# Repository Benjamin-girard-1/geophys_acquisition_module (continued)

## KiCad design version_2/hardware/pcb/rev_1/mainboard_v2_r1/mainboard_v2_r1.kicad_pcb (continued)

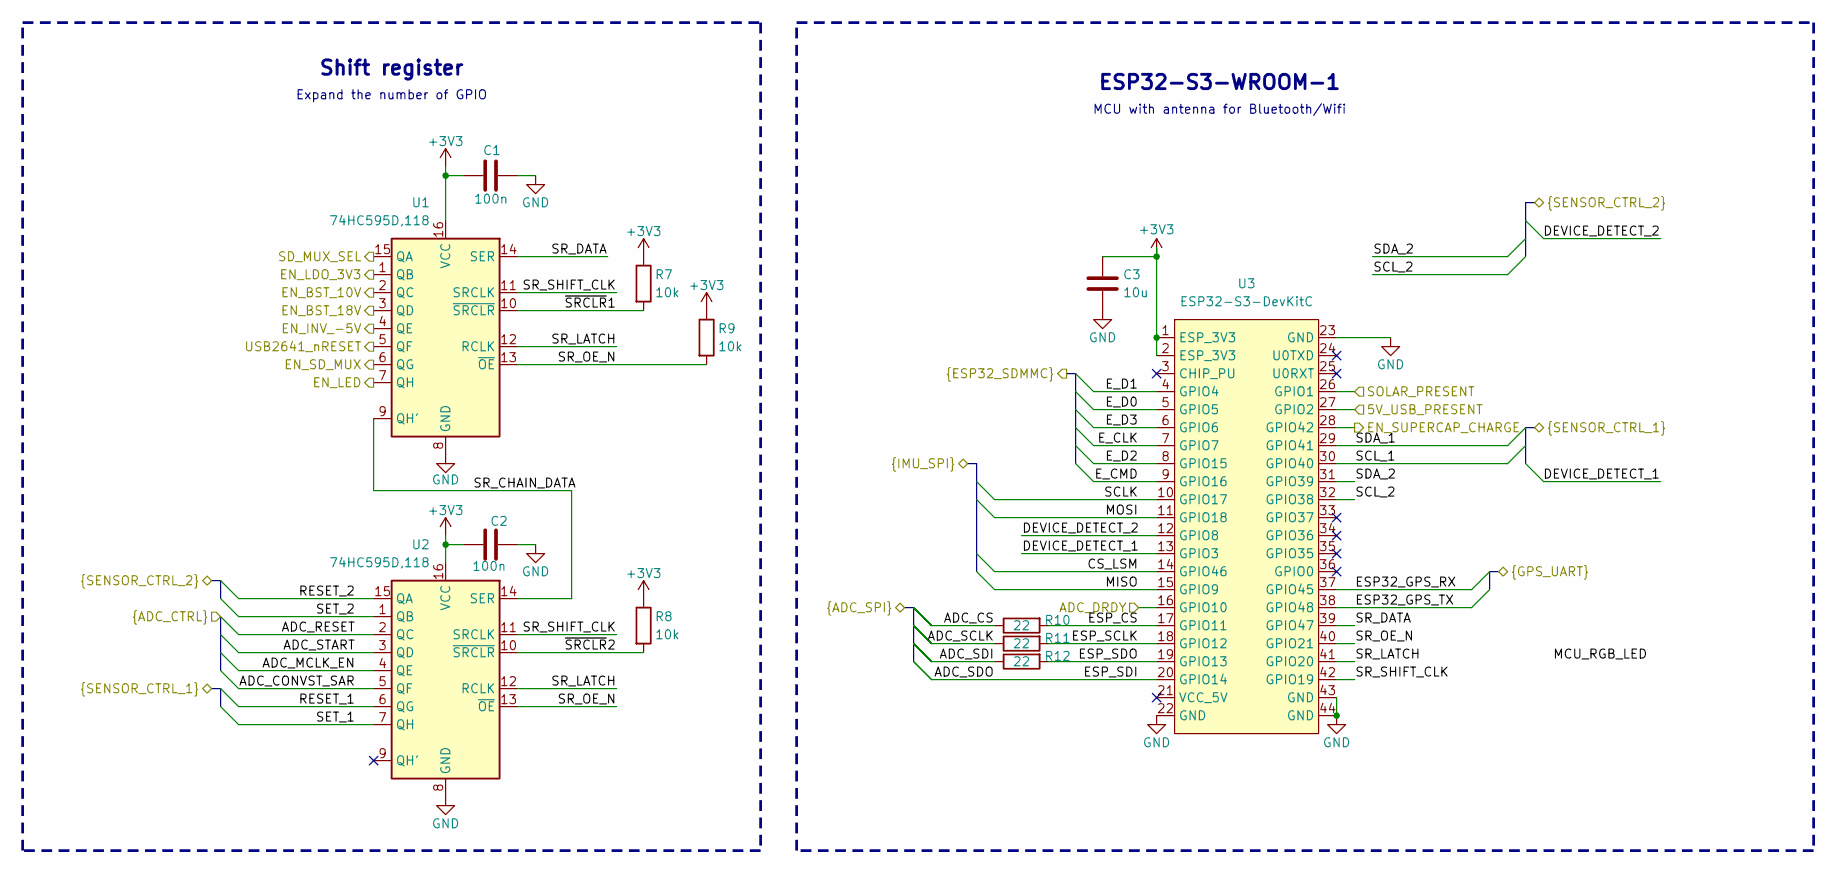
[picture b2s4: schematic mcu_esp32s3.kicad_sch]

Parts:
C1, C2: 100n; C_0603_1608Metric; LCSC C14663
C3: 10u; C_0805_2012Metric; LCSC C15850
R7, R8, R9: 10k; R_0603_1608Metric; LCSC C25804
R10, R11, R12: 22; R_0603_1608Metric; LCSC C23345
U1, U2: 74HC595D,118; SOIC-16_3.9x9.9mm_P1.27mm; LCSC C5947
U3: ESP32-S3-DevKitC; MODULE_ESP32-S3-DEVKITC

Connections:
+3V3: C1.1, C2.1, C3.1, R7.1, R8.1, R9.1, U1.16 (VCC), U2.16 (VCC), U3.1 (ESP_3V3), U3.2 (ESP_3V3); also elsewhere on the board
/ADC_AD777x/ADC_CONVST_SAR: U2.5 (QF); also elsewhere on the board
/ADC_AD777x/ADC_CS: R10.1; also elsewhere on the board
/ADC_AD777x/ADC_DRDY: U3.16 (GPIO10); also elsewhere on the board
/ADC_AD777x/ADC_MCLK_EN: U2.4 (QE); also elsewhere on the board
/ADC_AD777x/ADC_RESET: U2.2 (QC); also elsewhere on the board
/ADC_AD777x/ADC_SCLK: R11.1; also elsewhere on the board
/ADC_AD777x/ADC_SDI: R12.1; also elsewhere on the board
/ADC_AD777x/ADC_SDO: U3.20 (GPIO14); also elsewhere on the board
/ADC_AD777x/ADC_START: U2.3 (QD); also elsewhere on the board
/DATA_SAVING/EN_SD_MUX: U1.6 (QG); also elsewhere on the board
/DATA_SAVING/E_CLK: U3.7 (GPIO7); also elsewhere on the board
/DATA_SAVING/E_CMD: U3.9 (GPIO16); also elsewhere on the board
/DATA_SAVING/E_D0: U3.5 (GPIO5); also elsewhere on the board
/DATA_SAVING/E_D1: U3.4 (GPIO4); also elsewhere on the board
/DATA_SAVING/E_D2: U3.8 (GPIO15); also elsewhere on the board
/DATA_SAVING/E_D3: U3.6 (GPIO6); also elsewhere on the board
/DATA_SAVING/SD_MUX_SEL: U1.15 (QA); also elsewhere on the board
/DATA_SAVING/USB2641_nRESET: U1.5 (QF); also elsewhere on the board
/DEVICE_DETECT_1: U3.13 (GPIO3); also elsewhere on the board
/DEVICE_DETECT_2: U3.12 (GPIO8); also elsewhere on the board
/GNSS/ESP32_GPS_RX: U3.37 (GPIO45); also elsewhere on the board
/GNSS/ESP32_GPS_TX: U3.38 (GPIO48); also elsewhere on the board
/IMU/CS_LSM: U3.14 (GPIO46); also elsewhere on the board
/IMU/MISO: U3.15 (GPIO9); also elsewhere on the board
/IMU/MOSI: U3.11 (GPIO18); also elsewhere on the board
/IMU/SCLK: U3.10 (GPIO17); also elsewhere on the board
/IO_CONNECTOR/EN_LED: U1.7 (QH); also elsewhere on the board
/MCU_ESP32S3/5V_USB_PRESENT: U3.27 (GPIO2); also elsewhere on the board
/MCU_ESP32S3/EN_BST_10V: U1.2 (QC); also elsewhere on the board
/MCU_ESP32S3/EN_BST_18V: U1.3 (QD); also elsewhere on the board
/MCU_ESP32S3/EN_INV_-5V: U1.4 (QE); also elsewhere on the board
/MCU_ESP32S3/EN_LDO_3V3: U1.1 (QB); also elsewhere on the board
/MCU_ESP32S3/EN_SUPERCAP_CHARGE: U3.28 (GPIO42); also elsewhere on the board
/MCU_ESP32S3/ESP_CS: R10.2, U3.17 (GPIO11)
/MCU_ESP32S3/ESP_SCLK: R11.2, U3.18 (GPIO12)
/MCU_ESP32S3/ESP_SDO: R12.2, U3.19 (GPIO13)
/MCU_ESP32S3/SOLAR_PRESENT: U3.26 (GPIO1); also elsewhere on the board
/MCU_ESP32S3/SR_CHAIN_DATA: U1.9 (QH'), U2.14 (SER)
/MCU_ESP32S3/SR_DATA: U1.14 (SER), U3.39 (GPIO47)
/MCU_ESP32S3/SR_LATCH: U1.12 (RCLK), U2.12 (RCLK), U3.41 (GPIO20)
/MCU_ESP32S3/SR_OE_N: R9.2, U1.13 (~OE), U2.13 (~OE), U3.40 (GPIO21)
/MCU_ESP32S3/SR_SHIFT_CLK: U1.11 (SRCLK), U2.11 (SRCLK), U3.42 (GPIO19)
/MCU_ESP32S3/~SRCLR1: R7.2, U1.10 (~SRCLR)
/MCU_ESP32S3/~SRCLR2: R8.2, U2.10 (~SRCLR)
/RESET_1: U2.6 (QG); also elsewhere on the board
/RESET_2: U2.15 (QA); also elsewhere on the board
/SCL_1: U3.30 (GPIO40); also elsewhere on the board
/SCL_2: U3.32 (GPIO38); also elsewhere on the board
/SDA_1: U3.29 (GPIO41); also elsewhere on the board
/SDA_2: U3.31 (GPIO39); also elsewhere on the board
/SET_1: U2.7 (QH); also elsewhere on the board
/SET_2: U2.1 (QB); also elsewhere on the board
GND: C1.2, C2.2, C3.2, U1.8 (GND), U2.8 (GND), U3.22 (GND), U3.23 (GND), U3.43 (GND), U3.44 (GND); also elsewhere on the board

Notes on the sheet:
Shift register
Expand the number of GPIO
ESP32-S3-WROOM-1
MCU with antenna for Bluetooth/Wifi

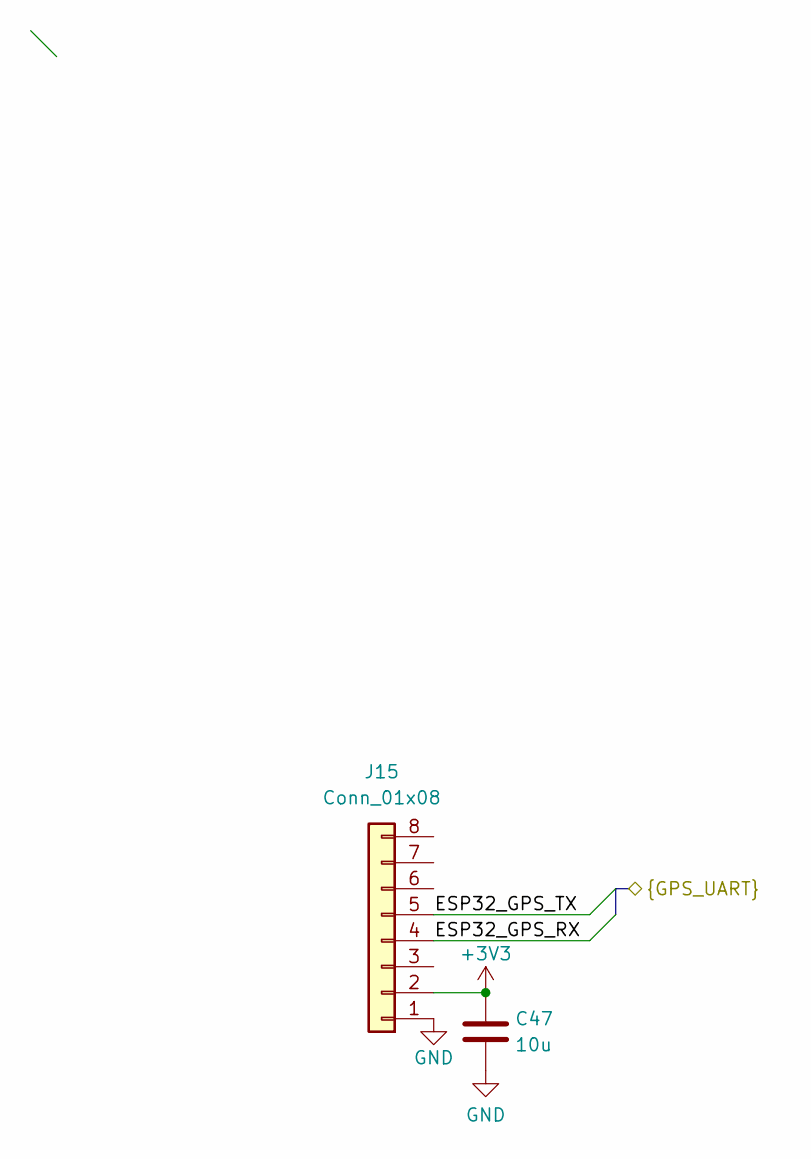
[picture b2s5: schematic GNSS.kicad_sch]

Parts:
C47: 10u; C_0805_2012Metric; LCSC C15850
J15: Conn_01x08; MAX_M10S_WITH_HEADER

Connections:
+3V3: C47.1, J15.2; also elsewhere on the board
/GNSS/ESP32_GPS_RX: J15.4; also elsewhere on the board
/GNSS/ESP32_GPS_TX: J15.5; also elsewhere on the board
GND: C47.2, J15.1; also elsewhere on the board

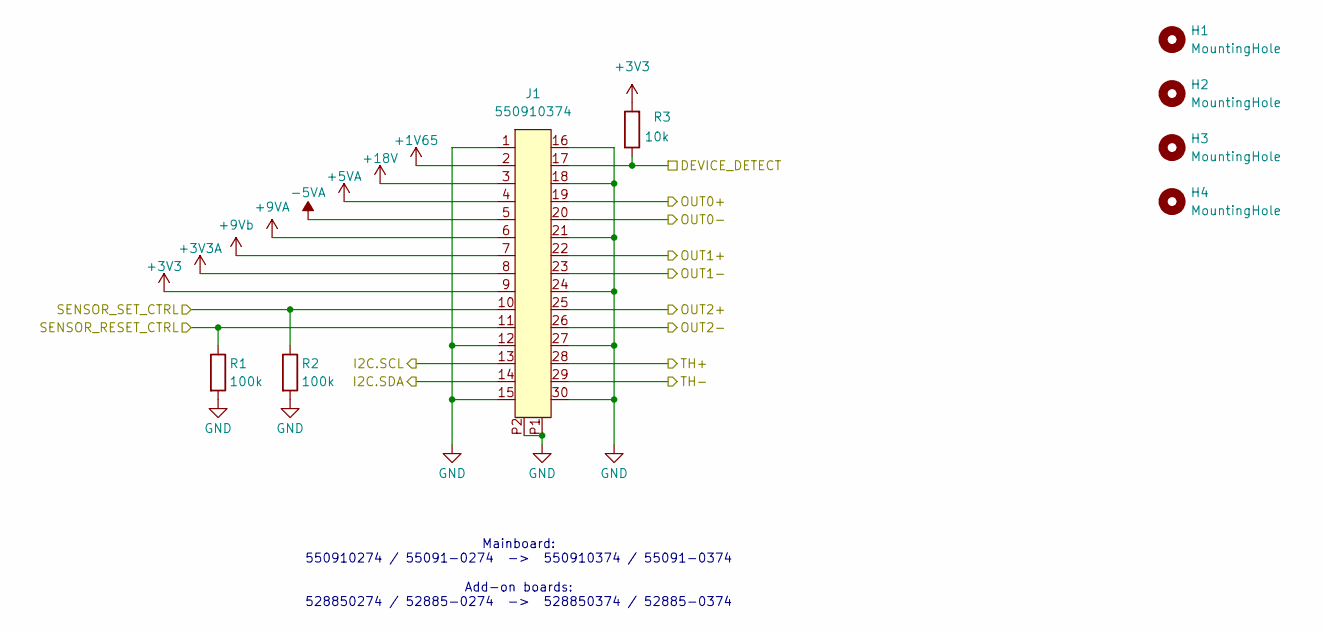
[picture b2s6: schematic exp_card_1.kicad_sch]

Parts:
H1, H2, H3, H4: MountingHole; MountingHole_4.3mm_M4
J1: 550910374; CON_550910374_MOL
R1, R2: 100k; R_0603_1608Metric; LCSC C25803
R3: 10k; R_0603_1608Metric; LCSC C25804

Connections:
+1V65: J1.2; also elsewhere on the board
+3V3: J1.9, R3.2; also elsewhere on the board
+3V3A: J1.8; also elsewhere on the board
+5VA: J1.4; also elsewhere on the board
+9VA: J1.6; also elsewhere on the board
+9Vb: J1.7; also elsewhere on the board
+18V: J1.3; also elsewhere on the board
-5VA: J1.5; also elsewhere on the board
/ADC_AD777x/AIN0+: J1.25; also elsewhere on the board
/ADC_AD777x/AIN0-: J1.26; also elsewhere on the board
/ADC_AD777x/AIN1+: J1.22; also elsewhere on the board
/ADC_AD777x/AIN1-: J1.23; also elsewhere on the board
/ADC_AD777x/AIN2+: J1.19; also elsewhere on the board
/ADC_AD777x/AIN2-: J1.20; also elsewhere on the board
/ADC_AD777x/TH1+: J1.28; also elsewhere on the board
/ADC_AD777x/TH1-: J1.29; also elsewhere on the board
/DEVICE_DETECT_1: J1.17, R3.1; also elsewhere on the board
/RESET_1: J1.11, R1.1; also elsewhere on the board
/SCL_1: J1.13; also elsewhere on the board
/SDA_1: J1.14; also elsewhere on the board
/SET_1: J1.10, R2.1; also elsewhere on the board
GND: J1.1, J1.12, J1.15, J1.16, J1.18, J1.21, J1.24, J1.27, J1.30, J1.P1, J1.P2, R1.2, R2.2; also elsewhere on the board

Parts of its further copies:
H5, H6, H7, H8: MountingHole; MountingHole_4.3mm_M4
J2: 550910374; CON_550910374_MOL
R4, R5: 100k; R_0603_1608Metric; LCSC C25803
R6: 10k; R_0603_1608Metric; LCSC C25804

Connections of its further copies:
+1V65: J2.2; also elsewhere on the board
+3V3: J2.9, R6.2; also elsewhere on the board
+3V3A: J2.8; also elsewhere on the board
+5VA: J2.4; also elsewhere on the board
+9VA: J2.6; also elsewhere on the board
+9Vb: J2.7; also elsewhere on the board
+18V: J2.3; also elsewhere on the board
-5VA: J2.5; also elsewhere on the board
/ADC_AD777x/AIN4+: J2.25; also elsewhere on the board
/ADC_AD777x/AIN4-: J2.26; also elsewhere on the board
/ADC_AD777x/AIN5+: J2.22; also elsewhere on the board
/ADC_AD777x/AIN5-: J2.23; also elsewhere on the board
/ADC_AD777x/AIN6+: J2.19; also elsewhere on the board
/ADC_AD777x/AIN6-: J2.20; also elsewhere on the board
/ADC_AD777x/TH2+: J2.28; also elsewhere on the board
/ADC_AD777x/TH2-: J2.29; also elsewhere on the board
/DEVICE_DETECT_2: J2.17, R6.1; also elsewhere on the board
/RESET_2: J2.11, R4.1; also elsewhere on the board
/SCL_2: J2.13; also elsewhere on the board
/SDA_2: J2.14; also elsewhere on the board
/SET_2: J2.10, R5.1; also elsewhere on the board
GND: J2.1, J2.12, J2.15, J2.16, J2.18, J2.21, J2.24, J2.27, J2.30, J2.P1, J2.P2, R4.2, R5.2; also elsewhere on the board

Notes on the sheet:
Mainboard: 550910274 / 55091-0274 -> 550910374 / 55091-0374 Add-on boards: 528850274 / 52885-0274 -> 528850374 / 52885-0374

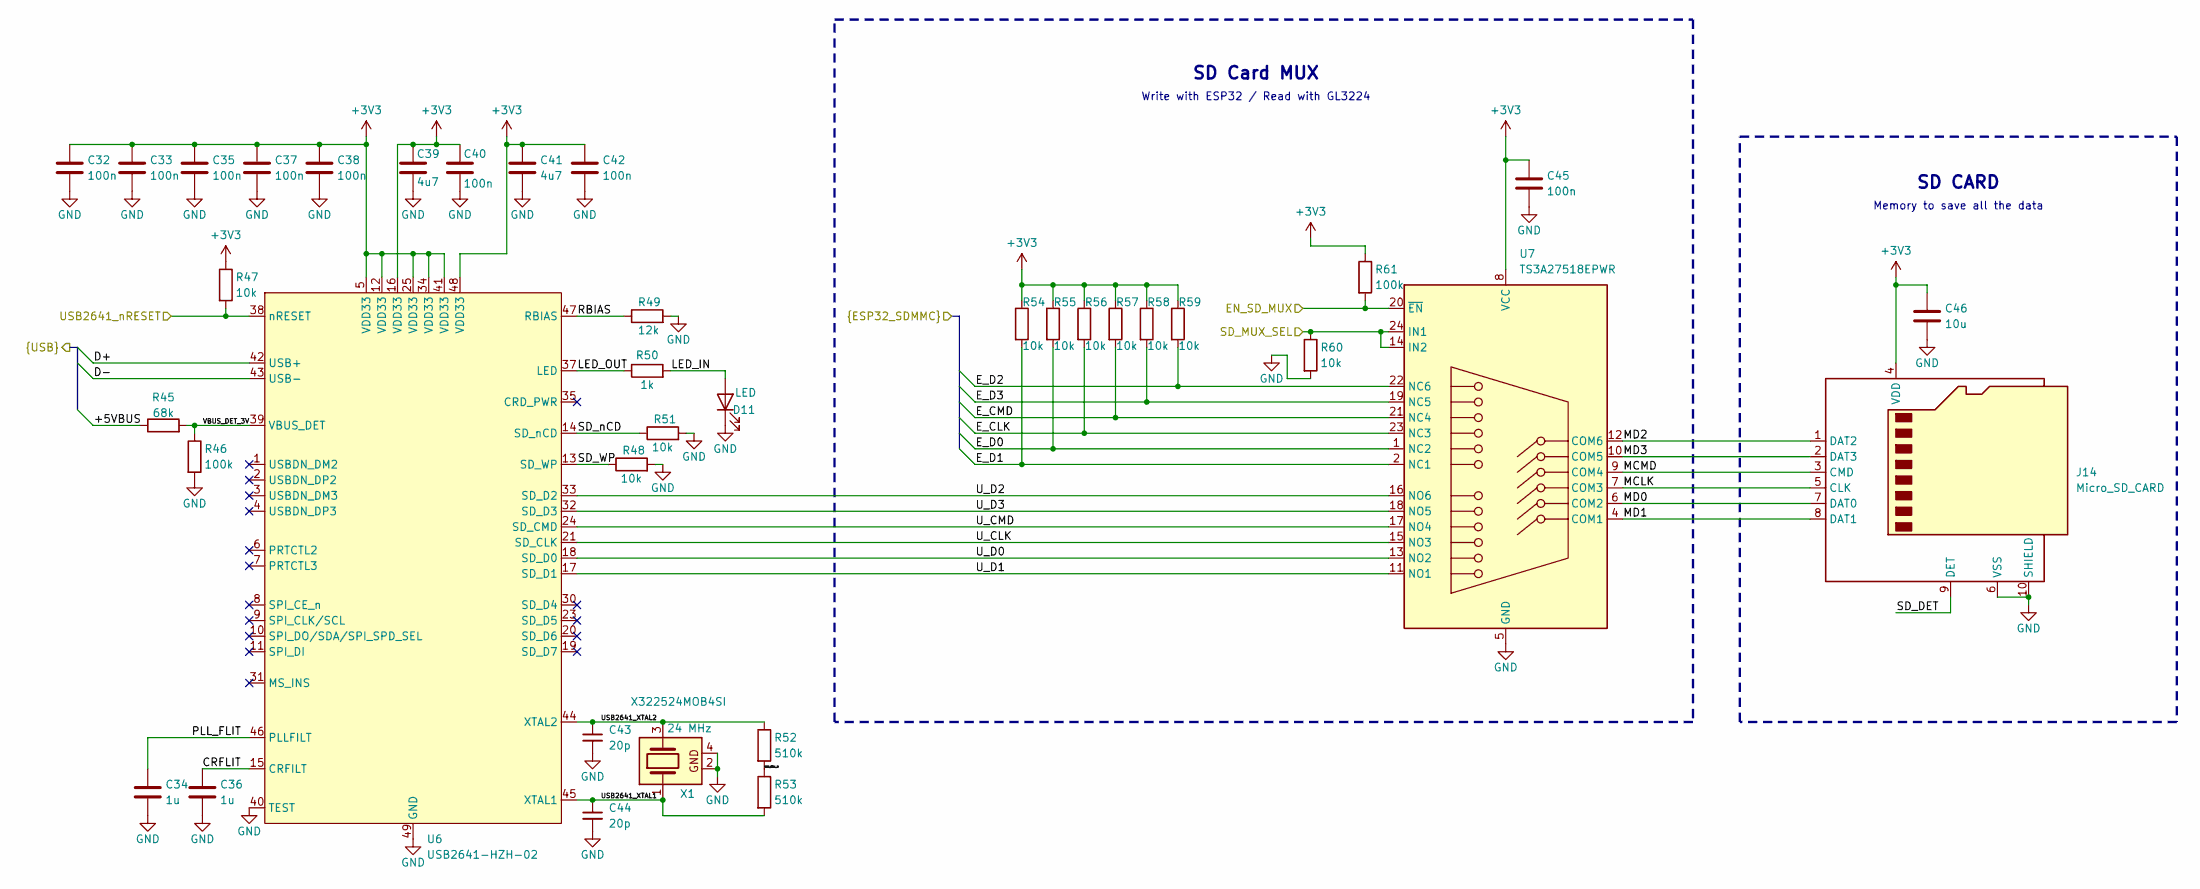
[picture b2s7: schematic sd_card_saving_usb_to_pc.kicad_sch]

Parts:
C32, C33, C35, C37, C38, C40, C42, C45: 100n; C_0603_1608Metric; LCSC C14663
C34, C36: 1u; C_0805_2012Metric; LCSC C28323
C39, C41: 4u7; C_1206_3216Metric; LCSC C29823
C43, C44: 20p; C_0402_1005Metric; LCSC C1554
C46: 10u; C_0805_2012Metric; LCSC C15850
D11: LED; LED_0805_2012Metric; LCSC C2296
J14: Micro_SD_CARD; CONN_503398-1892_MOL; LCSC C428492
R45: 68k; R_0603_1608Metric; LCSC C23231
R46, R61: 100k; R_0603_1608Metric; LCSC C25803
R47, R48, R51, R54, R55, R56, R57, R58, R59, R60: 10k; R_0603_1608Metric; LCSC C25804
R49: 12k; R_0603_1608Metric; LCSC C22790
R50: 1k; R_0603_1608Metric; LCSC C21190
R52, R53: 510k; R_0603_1608Metric; LCSC C23192
U6: USB2641-HZH-02; QFN-48-1EP_7x7mm_P0.5mm_EP5.3x5.3mm; LCSC C633596
U7: TS3A27518EPWR; TSSOP-24_4.4x7.8mm_P0.65mm; LCSC C443721
X1: X322524MOB4SI; Crystal_SMD_3225-4Pin_3.2x2.5mm; LCSC C70590

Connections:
+3V3: C32.1, C33.1, C35.1, C37.1, C38.1, C39.1, C40.1, C41.1, C42.1, C45.1, C46.1, J14.4 (VDD), R47.1, R54.1, R55.1, R56.1, R57.1, R58.1, R59.1, R61.1, U6.5 (VDD33), U6.12 (VDD33), U6.16 (VDD33), U6.25 (VDD33), U6.34 (VDD33), U6.41 (VDD33), U6.48 (VDD33), U7.8 (VCC); also elsewhere on the board
/DATA_SAVING/+5VBUS: R45.1; also elsewhere on the board
/DATA_SAVING/CRFLIT: C36.1, U6.15 (CRFILT)
/DATA_SAVING/D+: U6.42 (USB+); also elsewhere on the board
/DATA_SAVING/D-: U6.43 (USB-); also elsewhere on the board
/DATA_SAVING/EN_SD_MUX: R61.2, U7.20 (~EN); also elsewhere on the board
/DATA_SAVING/E_CLK: R56.2, U7.23 (NC3); also elsewhere on the board
/DATA_SAVING/E_CMD: R57.2, U7.21 (NC4); also elsewhere on the board
/DATA_SAVING/E_D0: R55.2, U7.1 (NC2); also elsewhere on the board
/DATA_SAVING/E_D1: R54.2, U7.2 (NC1); also elsewhere on the board
/DATA_SAVING/E_D2: R59.2, U7.22 (NC6); also elsewhere on the board
/DATA_SAVING/E_D3: R58.2, U7.19 (NC5); also elsewhere on the board
/DATA_SAVING/LED_IN: D11.2 (A), R50.2
/DATA_SAVING/LED_OUT: R50.1, U6.37 (LED)
/DATA_SAVING/MCLK: J14.5 (CLK), U7.7 (COM3)
/DATA_SAVING/MCMD: J14.3 (CMD), U7.9 (COM4)
/DATA_SAVING/MD0: J14.7 (DAT0), U7.6 (COM2)
/DATA_SAVING/MD1: J14.8 (DAT1), U7.4 (COM1)
/DATA_SAVING/MD2: J14.1 (DAT2), U7.12 (COM6)
/DATA_SAVING/MD3: J14.2 (DAT3), U7.10 (COM5)
/DATA_SAVING/PLL_FLIT: C34.1, U6.46 (PLLFILT)
/DATA_SAVING/RBIAS: R49.1, U6.47 (RBIAS)
/DATA_SAVING/SD_DET: J14.9 (DET)
/DATA_SAVING/SD_MUX_SEL: R60.1, U7.14 (IN2), U7.24 (IN1); also elsewhere on the board
/DATA_SAVING/SD_WP: R48.1, U6.13 (SD_WP)
/DATA_SAVING/SD_nCD: R51.1, U6.14 (SD_nCD)
/DATA_SAVING/USB2641_XTAL1: C44.1, R53.2, U6.45 (XTAL1), X1.1
/DATA_SAVING/USB2641_XTAL2: C43.1, R52.1, U6.44 (XTAL2), X1.3
/DATA_SAVING/USB2641_nRESET: R47.2, U6.38 (nRESET); also elsewhere on the board
/DATA_SAVING/USB_XTAL_R: R52.2, R53.1
/DATA_SAVING/U_CLK: U6.21 (SD_CLK), U7.15 (NO3)
/DATA_SAVING/U_CMD: U6.24 (SD_CMD), U7.17 (NO4)
/DATA_SAVING/U_D0: U6.18 (SD_D0), U7.13 (NO2)
/DATA_SAVING/U_D1: U6.17 (SD_D1), U7.11 (NO1)
/DATA_SAVING/U_D2: U6.33 (SD_D2), U7.16 (NO6)
/DATA_SAVING/U_D3: U6.32 (SD_D3), U7.18 (NO5)
/DATA_SAVING/VBUS_DET_3V: R45.2, R46.1, U6.39 (VBUS_DET)
GND: C32.2, C33.2, C34.2, C35.2, C36.2, C37.2, C38.2, C39.2, C40.2, C41.2, C42.2, C43.2, C44.2, C45.2, C46.2, D11.1 (K), J14.6 (VSS), J14.10 (SHIELD), J14.11 (VSS), J14.12 (VSS), J14.13 (VSS), J14.14 (VSS), R46.2, R48.2, R49.2, R51.2, R60.2, U6.40 (TEST), U6.49 (GND), U7.5 (GND), X1.2, X1.4; also elsewhere on the board

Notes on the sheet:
SD CARD
SD Card MUX
Memory to save all the data
Write with ESP32 / Read with GL3224

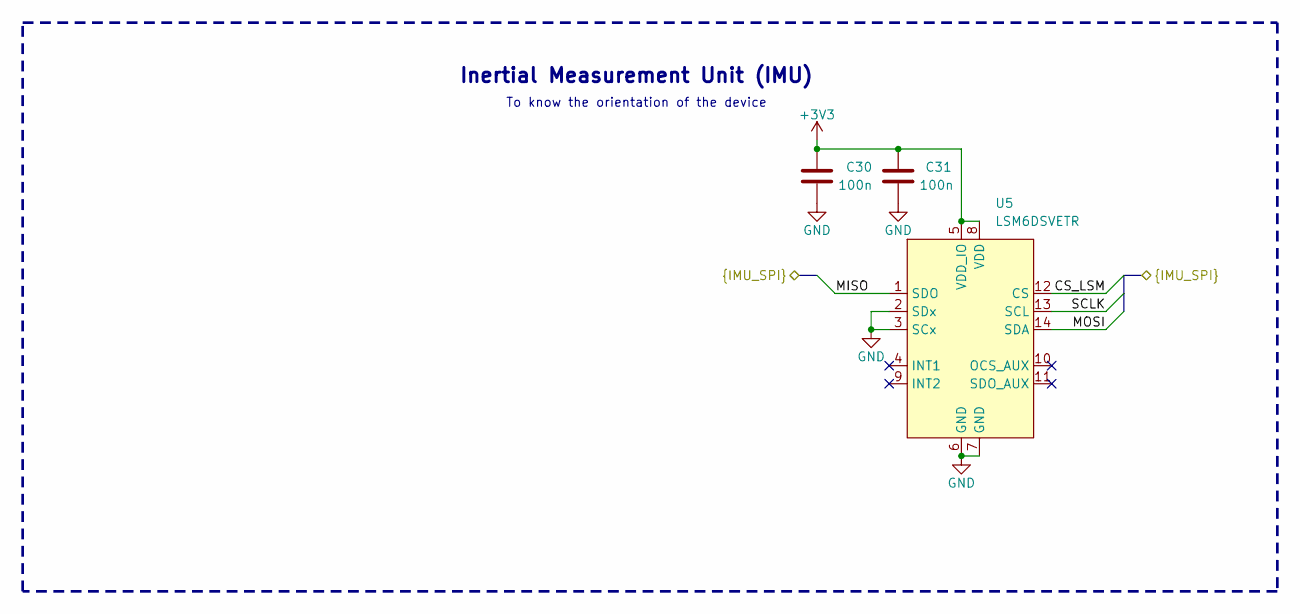
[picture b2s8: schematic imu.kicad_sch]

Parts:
C30, C31: 100n; C_0603_1608Metric; LCSC C14663
U5: LSM6DSVETR; LGA-14_3x2.5mm_P0.5mm_LayoutBorder3x4y; LCSC C41785564

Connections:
+3V3: C30.2, C31.2, U5.5 (VDD_IO), U5.8 (VDD); also elsewhere on the board
/IMU/CS_LSM: U5.12 (CS); also elsewhere on the board
/IMU/MISO: U5.1 (SDO); also elsewhere on the board
/IMU/MOSI: U5.14 (SDA); also elsewhere on the board
/IMU/SCLK: U5.13 (SCL); also elsewhere on the board
GND: C30.1, C31.1, U5.2 (SDx), U5.3 (SCx), U5.6 (GND), U5.7 (GND); also elsewhere on the board

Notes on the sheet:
Inertial Measurement Unit (IMU)
To know the orientation of the device

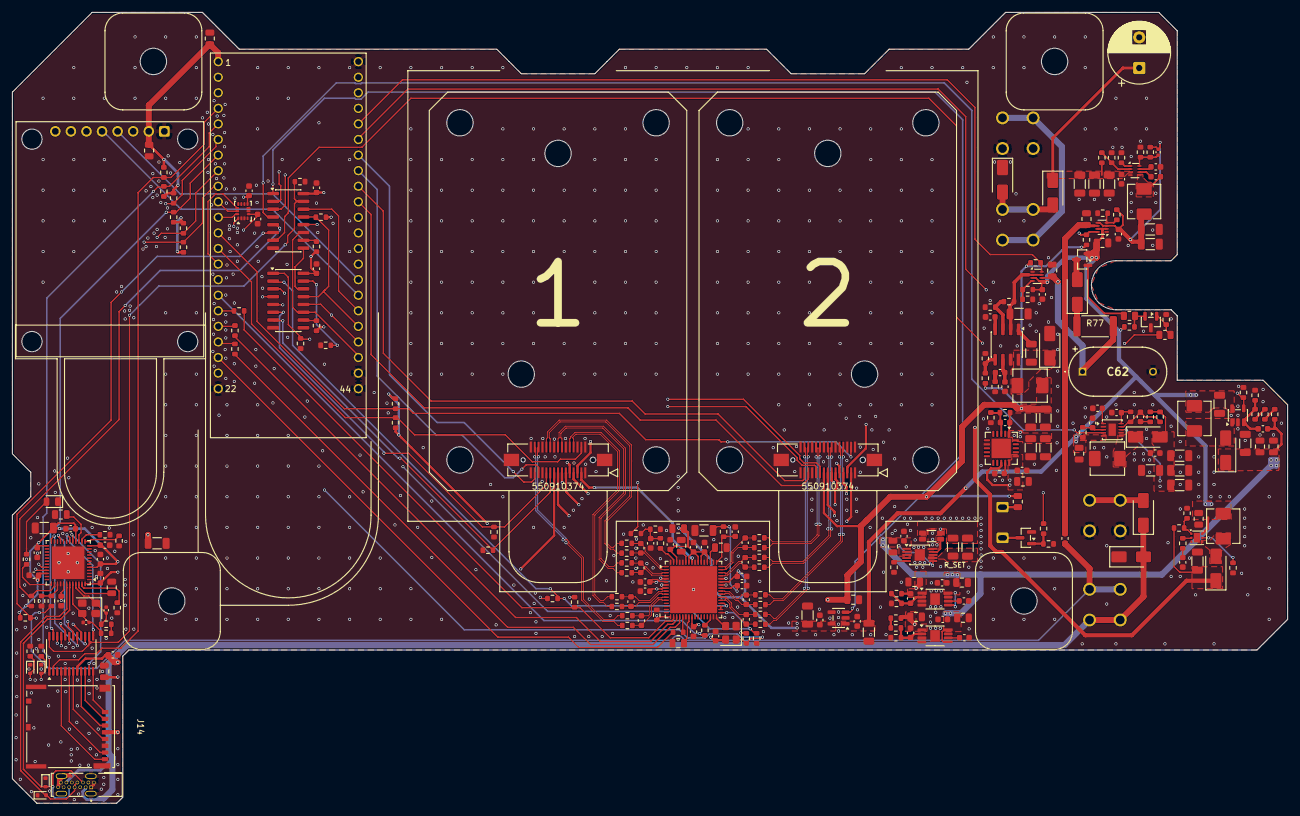
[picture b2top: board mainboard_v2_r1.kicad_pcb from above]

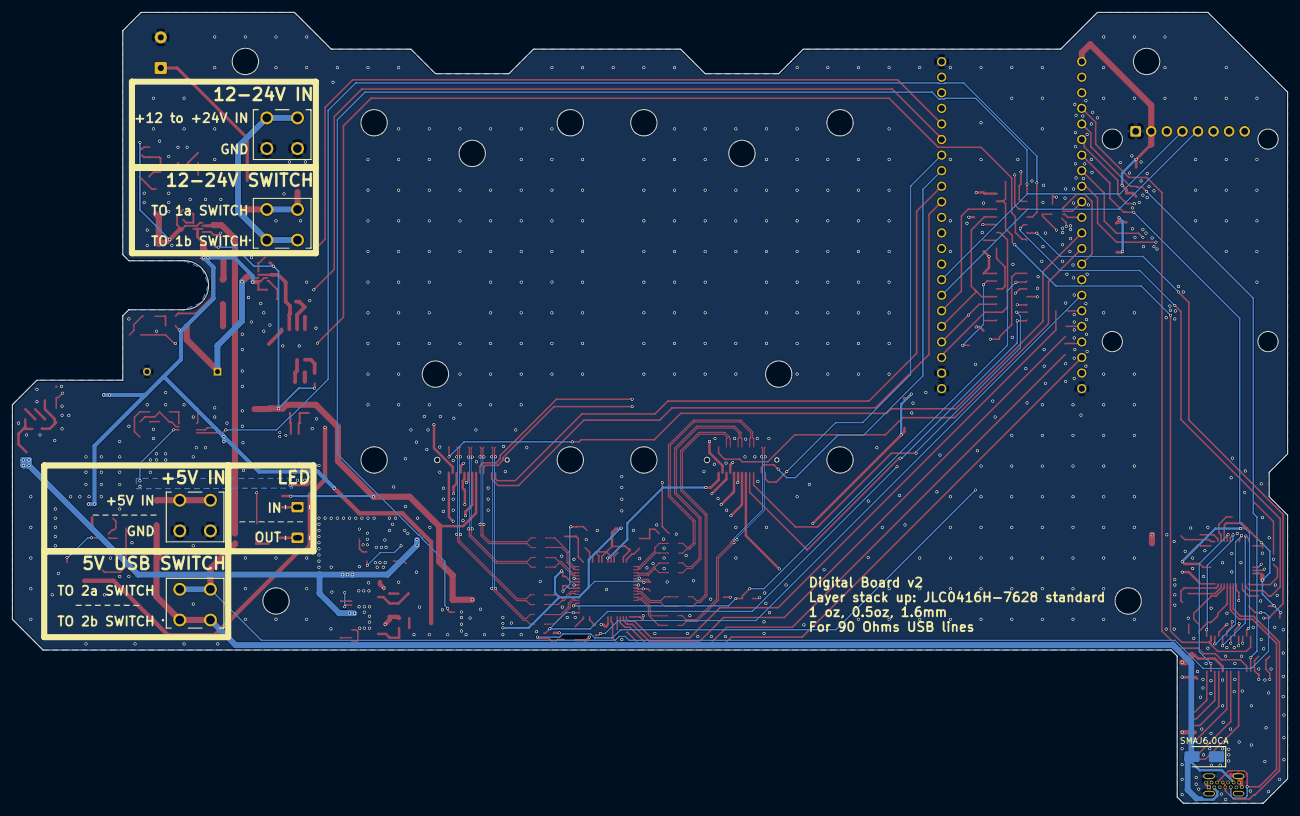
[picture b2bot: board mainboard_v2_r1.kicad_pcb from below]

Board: 4 copper layers, 208.0 x 129.0 mm, 287 parts (7 on the bottom side), 192 nets.
